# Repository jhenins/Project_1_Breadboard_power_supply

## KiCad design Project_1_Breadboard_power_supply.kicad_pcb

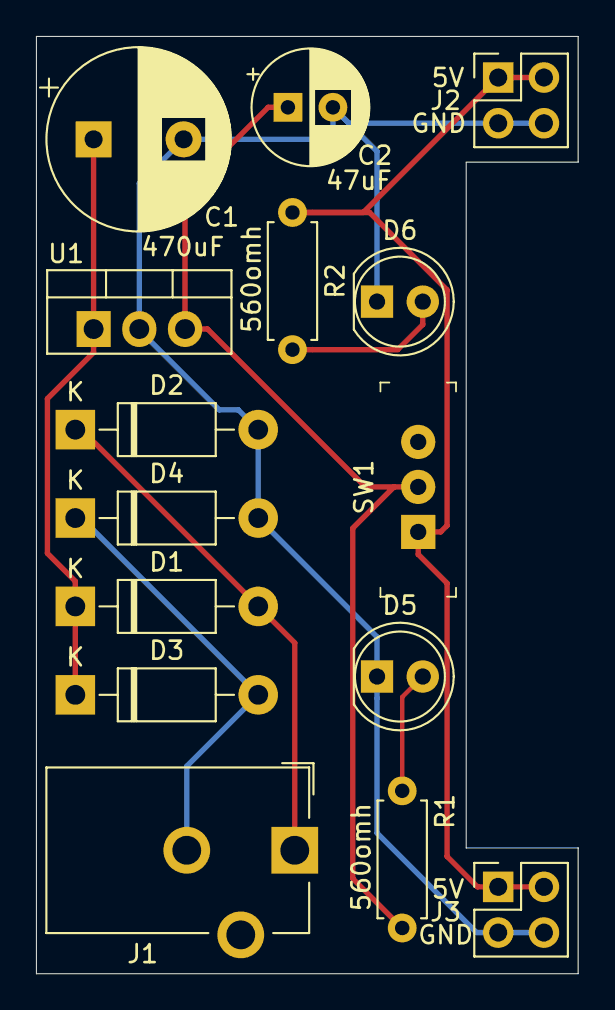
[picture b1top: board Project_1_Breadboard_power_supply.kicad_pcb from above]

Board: 2 copper layers, 30.1 x 52.1 mm, 15 parts (0 on the bottom side), 8 nets.

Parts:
C1: CP; CP_Radial_D10.0mm_P5.00mm
C2: CP; CP_Radial_D6.3mm_P2.50mm
D1, D2, D3, D4: 1N4007; D_DO-41_SOD81_P10.16mm_Horizontal
D5, D6: LED; LED_D5.0mm
J1: Barrel_Jack_Switch; BarrelJack_CUI_PJ-102AH_Horizontal
J2, J3: Conn_02x02_Odd_Even; PinHeader_2x02_P2.54mm_Vertical
R1, R2: R; R_Axial_DIN0207_L6.3mm_D2.5mm_P7.62mm_Horizontal
SW1: SW_DPDT_x2; Switch_Slide_11.6x4mm_EG1218
U1: LM7805_TO220; TO-220-3_Vertical

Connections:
/V-: C1.2, C2.2, D2.2, D4.2, D5.1, D6.1, J2.3, J2.4, J3.3, J3.4, U1.2
/Vin: C1.1, D1.1, D3.1, U1.1
/Vout1: C2.1, R1.2, SW1.2, U1.3
/Vout2: J2.1, J2.2, J3.1, J3.2, R2.1, SW1.1
unnamed: D1.2, D2.1, J1.1
unnamed: D3.2, D4.1, J1.2
unnamed: D5.2, R1.1
unnamed: D6.2, R2.2

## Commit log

2019-10-17 First commit!
